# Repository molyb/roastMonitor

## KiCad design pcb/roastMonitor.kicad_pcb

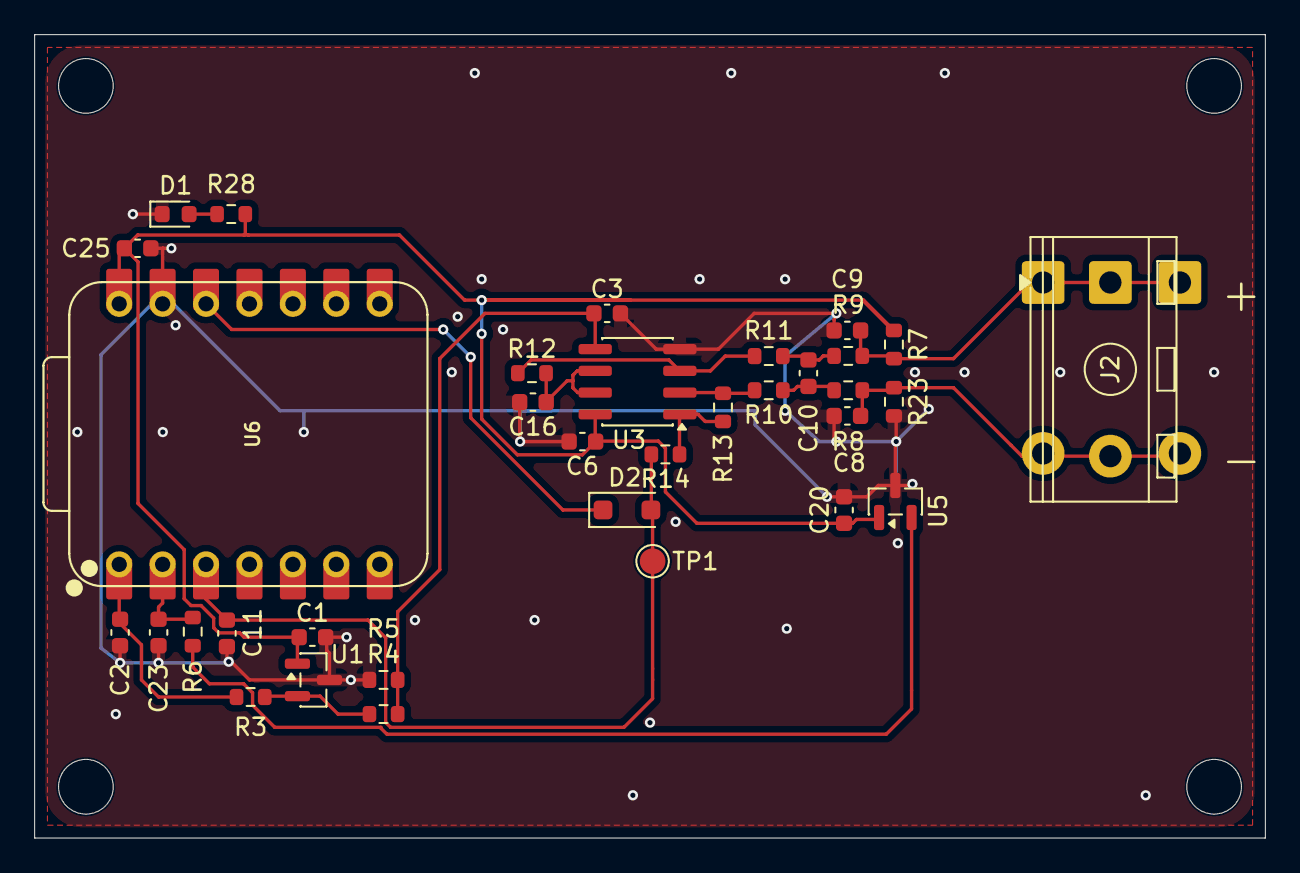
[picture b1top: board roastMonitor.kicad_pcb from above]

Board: 2 copper layers, 72.0 x 47.0 mm, 38 parts (0 on the bottom side), 18 nets.

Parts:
C1, C3, C6, C8, C9, C10, C16, C20, C25: 100n; C_0603_1608Metric
C2, C11, C23: 1u; C_0603_1608Metric
D1: LED; LED_0603_1608Metric
D2: D; D_SOD-123F
H1, H2, H3, H4: MountingHole; MountingHole_3.2mm_M3
J2: Conn_01x02; TerminalBlock_RND_205-00241_1x02_P10.16mm_Horizontal
R3, R6, R14: 1k; R_0603_1608Metric
R4, R5, R12, R13: 100k±0.1%; R_0603_1608Metric
R7: 10M; R_0603_1608Metric
R8, R9: 100±0.1%; R_0603_1608Metric
R10, R11: 1k±0.1%; R_0603_1608Metric
R23: 0; R_0603_1608Metric
R28: 470; R_0603_1608Metric
TP1: TestPoint; TestPoint_Pad_D1.5mm
U1: REF3040; SOT-23
U3: OPA2333xxD; SOIC-8_3.9x4.9mm_P1.27mm
U5: MCP9701A; SOT-23
U6: XIAO-ESP32-C3-DIP

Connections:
+5V: C1.1, C6.1, C20.1, C25.1, R7.1, R28.1, U1.1 (IN), U3.8 (V+), U5.1 (V_{DD}), U6.14 (VBUS)
/Vref: C2.1, R3.2, U6.1 (GPIO2_A0_D0)
/Vtemp: C23.1, R6.2, U6.2 (GPIO3_A1_D1)
/Vthermo1: C11.1, D2.2 (A), R14.2, TP1.1 (1_1), U6.3 (GPIO4_A2_D2)
/amp/ThermoCouple+: C9.1, J2.1, R7.2, R9.1
/amp/ThermoCouple-: C8.1, J2.2, R8.1, R23.1
/amp/Voffset: C16.1, R12.2, U3.6 (-), U3.7
GND: C1.2, C2.2, C3.2, C6.2, C8.2, C9.2, C11.2, C16.2, C20.2, C23.2, C25.2, D1.1 (K), R5.2, R23.2, U1.3 (GND), U3.4 (V-), U5.3 (GND), U6.13 (GND)
unnamed: C10.1, R8.2, R10.1
unnamed: C10.2, R9.2, R11.1
unnamed: D1.2 (A), R28.2
unnamed: D2.1 (K), U6.12 (3V3)
unnamed: R13.2, R14.1, U3.1
unnamed: R3.1, R4.1, U1.2 (OUT)
unnamed: R11.2, R12.1, U3.3 (+)
unnamed: R10.2, R13.1, U3.2 (-)
unnamed: C3.1, R4.2, R5.1, U3.5 (+)
unnamed: R6.1, U5.2 (V_{OUT})

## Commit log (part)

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2026-03-23 Add initial files
2026-03-26 Initial PCB design
2026-03-26 Update gitignore
2026-03-26 Add sample firmware
2026-03-30 Update PCB
2026-04-13 update value
2026-04-13 Add calc_voltage for thermo couple
2026-04-26 Update register values
2026-04-26 Implement voltage to temperature
2026-05-08 For debug
2026-05-09 add calc script
2026-05-09 Add debug outpout
2026-05-10 Show ThermoCouple temperature for debug
